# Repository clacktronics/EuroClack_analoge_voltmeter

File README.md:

# Clacktronics Analogue Voltmeter

Want your modular to look cool and vintage? Ever wanted to see what your slow evolving CV signal is doing or where it actually is?! Analogue meter is for you! Clacktronics Analogue meter is a partially assembled kit that contains the driving circuitry and the meter to add a Voltage needle meter into your rack. The meter itself is bipolar and able to measure +10V to -10V and the driving circuitry as a bonus offers 3 buffer mult outputs

* Width: 14HP
* Height: 3U
* Depth: 50mm

More information at [clacktronics.co.uk/euroclack](http://clacktronics.co.uk/euroclack)

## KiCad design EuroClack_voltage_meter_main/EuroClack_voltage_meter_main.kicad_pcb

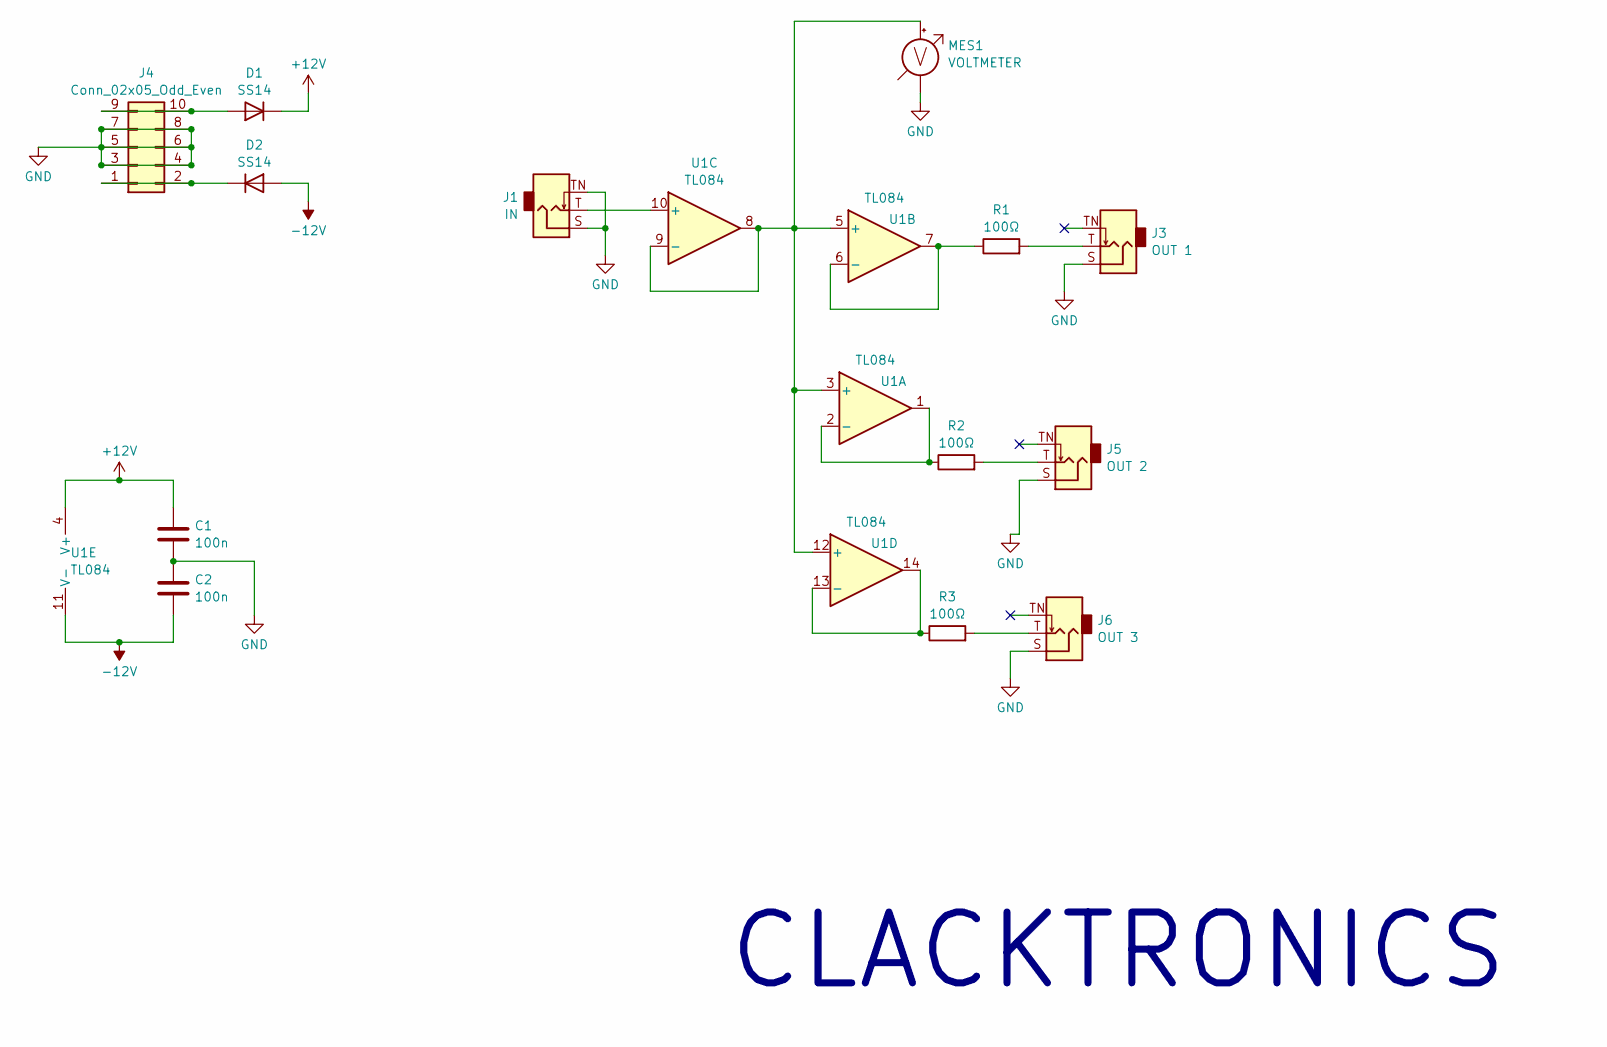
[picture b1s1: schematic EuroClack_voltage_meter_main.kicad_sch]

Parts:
C1, C2: 100n; C_0805_2012Metric
D1, D2: SS14; D_SMA
J1: IN; Jack_3.5mm_QingPu_WQP-PJ398SM_Vertical
J3: OUT 1; Jack_3.5mm_QingPu_WQP-PJ398SM_Vertical
J4: Conn_02x05_Odd_Even; IDC-Header_2x05_P2.54mm_Vertical
J5: OUT 2; Jack_3.5mm_QingPu_WQP-PJ398SM_Vertical
J6: OUT 3; Jack_3.5mm_QingPu_WQP-PJ398SM_Vertical
MES1: VOLTMETER; CONN-TH_2P-P3.81_DB125-3.81-2P-BK-S
R1, R2, R3: 100Ω; R_0603_1608Metric
U1: TL084; SO-14_3.9x8.65mm_P1.27mm

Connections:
+12V: C1.1, D1.1 (K), U1.4 (V+)
-12V: C2.2, D2.2 (A), U1.11 (V-)
GND: C1.2, C2.1, J1.S, J1.TN, J3.S, J4.3, J4.4, J4.5, J4.6, J4.7, J4.8, J5.S, J6.S, MES1.1 (-)
unnamed: D1.2 (A), J4.9, J4.10
unnamed: D2.1 (K), J4.1, J4.2
unnamed: J3.T, R1.2
unnamed: J5.T, R2.2
unnamed: J6.T, R3.2
unnamed: MES1.2 (+), U1.3 (+), U1.5 (+), U1.8, U1.9 (-), U1.12 (+)
unnamed: R2.1, U1.1, U1.2 (-)
unnamed: R1.1, U1.6 (-), U1.7
unnamed: J1.T, U1.10 (+)
unnamed: R3.1, U1.13 (-), U1.14

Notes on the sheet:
CLACKTRONICS

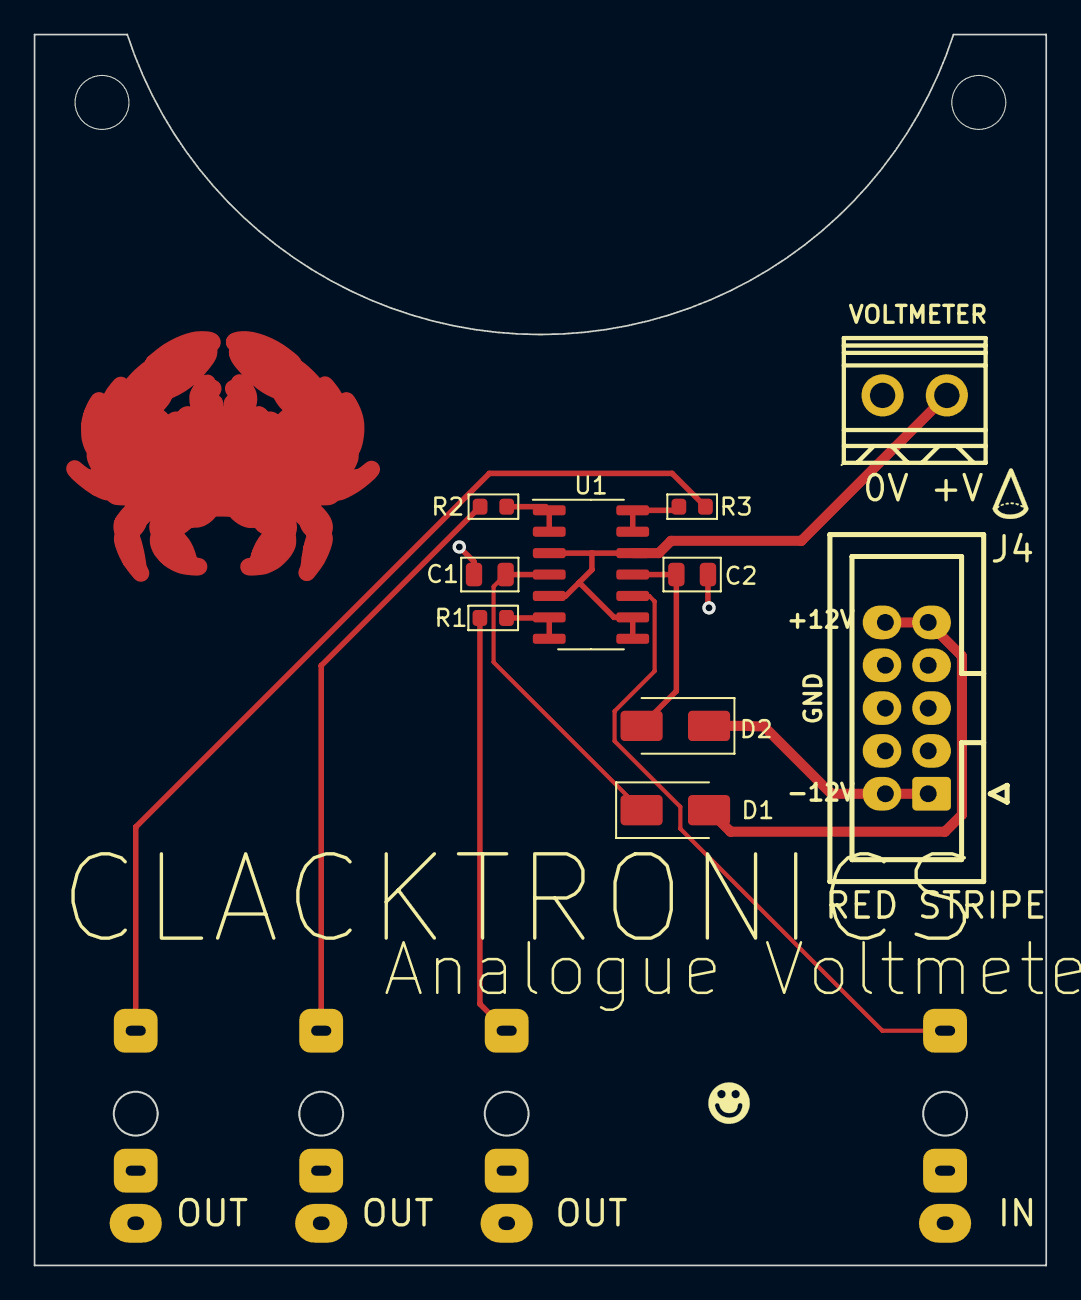
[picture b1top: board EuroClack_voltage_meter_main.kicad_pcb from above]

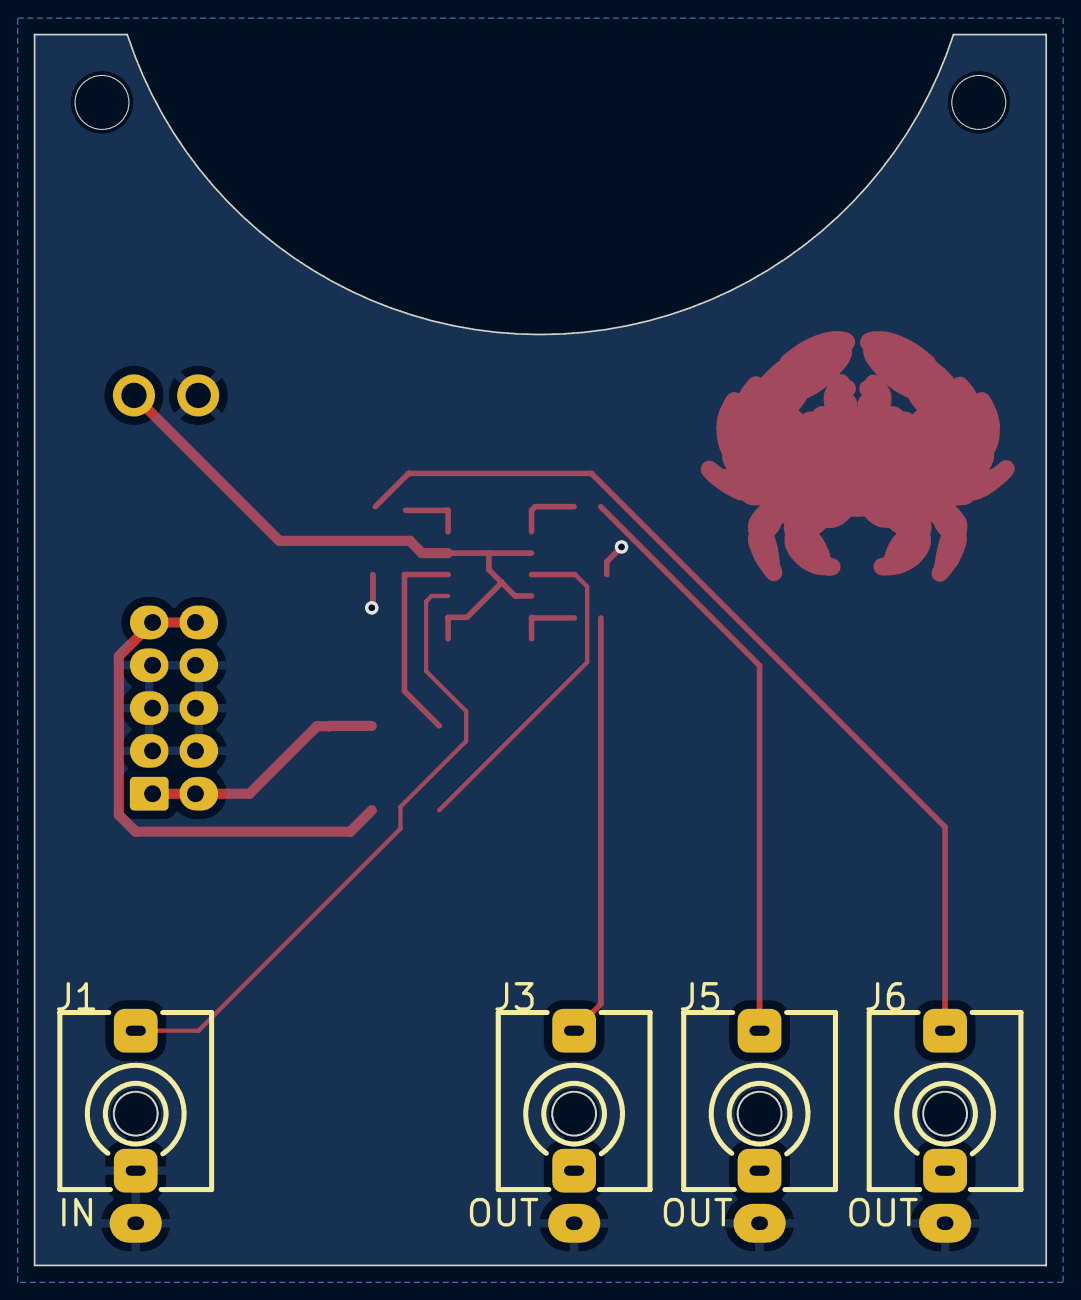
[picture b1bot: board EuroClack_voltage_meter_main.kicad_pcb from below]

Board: 2 copper layers, 60.0 x 73.0 mm, 14 parts (4 on the bottom side), 13 nets.

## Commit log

2024-05-03 Initital files
2024-05-03 add docs
2024-05-03 shuffle
